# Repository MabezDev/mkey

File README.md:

## mKey

A mechanical keyboard based on an ESP32-S3, with firmware written in Rust.

[Click here to view the PCB & Schematic interactively in the browser](https://kicanvas.org/?github=https%3A%2F%2Fgithub.com%2FMabezDev%2Fmkey%2Ftree%2Fmain%2Fhardware%2Fboard)

## Flashing

The USB port is intended for flashing, as well as software USB usage. Version 1.0 of the board however has the DP and DM pins swapped, therefore to flash the board from the factory (or if the flash is wiped for any reason) you must flash via UART0. The pinout is as follows:

- TX is connected to the input side of D2 (COL1)
- RX is conncted to the input side of D3 (COL2)

## License

Licensed under either of:

- Apache License, Version 2.0 ([LICENSE-APACHE](LICENSE-APACHE) or http://www.apache.org/licenses/LICENSE-2.0)
- MIT license ([LICENSE-MIT](LICENSE-MIT) or http://opensource.org/licenses/MIT)
- CERN-OHL for the hardware files

at your option.

### Contribution

Unless you explicitly state otherwise, any contribution intentionally submitted for inclusion in
the work by you, as defined in the Apache-2.0 license, shall be dual licensed as above, without
any additional terms or conditions.

Contributions to the hardware will be licensed under the CERN-OHL license.

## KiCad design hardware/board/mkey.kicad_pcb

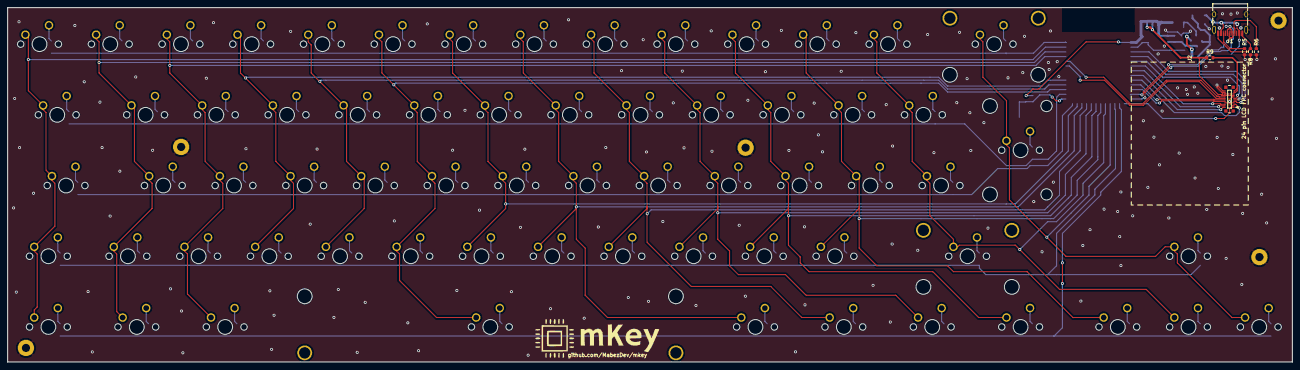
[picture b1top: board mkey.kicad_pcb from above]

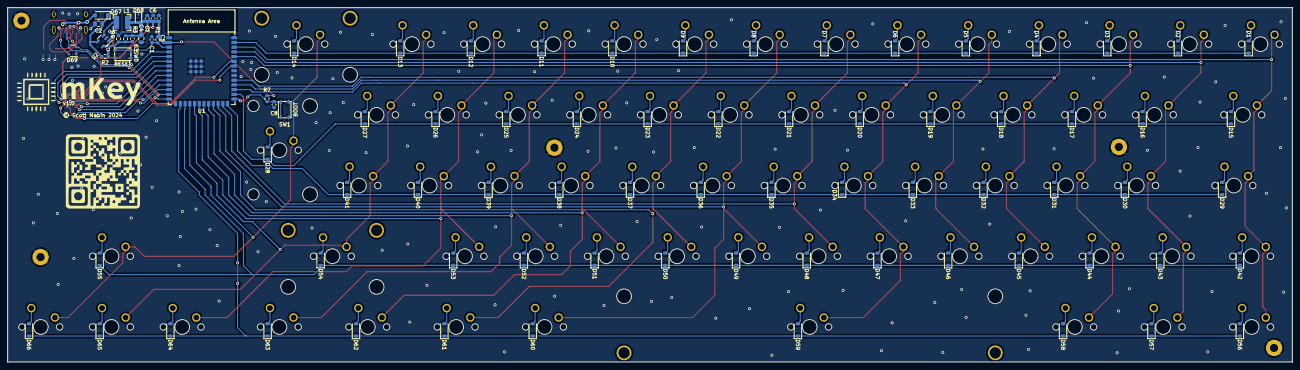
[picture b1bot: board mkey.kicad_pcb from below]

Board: 2 copper layers, 346.2 x 95.5 mm, 163 parts (87 on the bottom side), 112 nets.

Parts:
C1, C5: 1uF 16V; C_0603_1608Metric
C2, C4: 10uF 16V; C_0805_2012Metric
C3: 22pF 50V; C_0603_1608Metric
C6: 100nF 10V; C_0603_1608Metric
C7: 10nF 10V; C_0603_1608Metric
C8: 1nF 10V; C_0603_1608Metric
D1, D2, D3, D4, D5, D6, D7, D8, D9, D10, D11, D12, D13, D14, D15, D16, D17, D18, D19, D20, D21, D22, D23, D24, D25, D26, D27, D28, D29, D30, D31, D32, D33, D34, D35, D36, D37, D38, D39, D40, D41, D42, D43, D44, D45, D46, D47, D48, D49, D50, D51, D52, D53, D54, D55, D56, D57, D58, D59, D60, D61, D62, D63, D64, D65, D66: D_Small; D_SOD-123
D67: B5819W; D_SOD-123
D68: PESD3V3L1BA,115; D_SOD-323
D69: SP0503BAHT; SOT-143
J1: USB_C_REP_2.0; USB_C_Receptacle_HRO_TYPE-C-31-M-12
J2: 24 pin LCD FPC connector; CONN-SMD_24P-P0.40_X0400FVS-24-LPSN-LINEAR
L1: SPH4018H2R2MT (2.2uH 2.2A); L_Bourns-SRN4018
MX1, MX2, MX3, MX4, MX5, MX6, MX7, MX8, MX9, MX10, MX11, MX12, MX13, MX14, MX16, MX17, MX18, MX19, MX20, MX21, MX22, MX23, MX24, MX25, MX26, MX27, MX28, MX30, MX31, MX32, MX33, MX34, MX35, MX36, MX37, MX38, MX39, MX40, MX41, MX43, MX44, MX45, MX46, MX47, MX48, MX49, MX50, MX51, MX52, MX53, MX54, MX55, MX59, MX64, MX65, MX66: MX_SW_solder; SW_MX_1u
MX15: MX_SW_solder; SW_MX_1.5u
MX29: MX_SW_solder; SW_MX_1.75u
MX42, MX56, MX57, MX58, MX60, MX61, MX62, MX63: MX_SW_solder; SW_MX_1.25u
R1, R2, R7: 10kR 1%; R_0603_1608Metric
R3: 100kR 1%; R_0603_1608Metric
R4: 22k1R 1%; R_0603_1608Metric
R5, R6: 5k1R 1%; R_0603_1608Metric
R8: 0R 1%; R_0603_1608Metric
R9: 51.1R 1%; R_0603_1608Metric
S1: MX_stab; STAB_MX_P_6.25u
S2: MX_stab; STAB_MX_P_2u
S4: MX_stab; STAB_MX_P_2.75u
S5: MX_stab; STAB_MX_ISO-ROT
SW0, SW1: SW_Push; SW_SPST_PTS810
U1: ESP32-S3-WROOM-1
U2: SY8088; SOT-23-5

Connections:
+3V3: C3.1, C4.1, C5.1, C6.1, C7.1, D68.2 (A2), J2.9, J2.10, J2.15, J2.16, L1.2, R1.1, R3.1, R7.1, R9.2, U1.2 (3V3)
/Buck_Coil: L1.1, U2.3 (LX)
BOOT: C8.2, R7.2, SW1.1, U1.27 (GPIO0/BOOT)
CHIP_PU: C1.1, R1.2, SW0.1, U1.3 (EN)
COL0: MX1.1, MX15.1, MX29.1, MX42.1, MX56.1, U1.38 (GPIO2/TOUCH2/ADC1_CH1)
COL1: MX2.1, MX16.1, MX30.1, MX43.1, MX57.1, U1.37 (U0TXD/GPIO43/CLK_OUT1)
COL2: MX3.1, MX17.1, MX31.1, MX44.1, MX58.1, U1.36 (U0RXD/GPIO44/CLK_OUT2)
COL3: MX4.1, MX18.1, MX32.1, MX45.1, U1.31 (GPIO38/FSPIWP/SUBSPIWP)
COL4: MX5.1, MX19.1, MX33.1, MX46.1, U1.30 (SPIDQS/GPIO37/FSPIQ/SUBSPIQ)
COL5: MX6.1, MX20.1, MX34.1, MX47.1, MX59.1, U1.29 (SPIIO7/GPIO36/FSPICLK/SUBSPICLK)
COL6: MX7.1, MX21.1, MX35.1, MX48.1, U1.25 (GPIO48/SPICLK_N/SUBSPICLK_N_DIFF)
COL7: MX8.1, MX22.1, MX36.1, MX49.1, MX60.1, U1.24 (GPIO47/SPICLK_P/SUBSPICLK_P_DIFF)
COL8: MX9.1, MX23.1, MX37.1, MX50.1, MX61.1, U1.23 (GPIO21)
COL9: MX10.1, MX24.1, MX38.1, MX51.1, MX62.1, U1.22 (GPIO14/TOUCH14/ADC2_CH3/FSPIWP/FSPIDQS/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)
COL10: MX11.1, MX25.1, MX39.1, MX52.1, MX63.1, U1.21 (GPIO13/TOUCH13/ADC2_CH2/FSPIQ/FSPIIO7/S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)
COL11: MX12.1, MX26.1, MX40.1, MX53.1, MX64.1, U1.20 (GPIO12/TOUCH12/ADC2_CH1/FSPICLK/FSPIIO6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)
COL12: MX13.1, MX27.1, MX41.1, MX54.1, MX65.1, U1.19 (GPIO11/TOUCH11/ADC2_CH0/FSPID/FSPIIO5/S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)
COL13: MX14.1, MX28.1, MX55.1, MX66.1, U1.18 (GPIO10/TOUCH10/ADC1_CH9/FSPICS0/FSPIIO4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)
GND: C1.2, C2.2, C4.2, C5.2, C6.2, C7.2, C8.1, D68.1 (A1), D69.1 (A), J1.S1 (SHIELD), J2.2, J2.4, J2.8, J2.13, J2.14, J2.21, R4.2, R5.2, R6.2, R8.2, SW0.2, SW1.2, U1.1 (GND), U1.40 (GND), U1.41 (GND), U2.2 (GND)
LCD_CLK: J2.5, U1.4 (GPIO4/TOUCH4/ADC1_CH3)
LCD_D/C: J2.24, U1.9 (GPIO16/U0CTS/ADC2_CH5/XTAL_32K_N)
LCD_RESET: J2.1, U1.15 (GPIO3/TOUCH3/ADC1_CH2)
LCD_SIO0: J2.7, U1.6 (GPIO6/TOUCH6/ADC1_CH5)
LCD_SIO1: J2.6, U1.5 (GPIO5/TOUCH5/ADC1_CH4)
LCD_SIO2: J2.23, U1.8 (GPIO15/U0RTS/ADC2_CH4/XTAL_32K_P)
LCD_SIO3: J2.22, U1.7 (GPIO7/TOUCH7/ADC1_CH6)
unnamed: D1.2 (A), MX1.2
unnamed: D2.2 (A), MX2.2
unnamed: D3.2 (A), MX3.2
unnamed: D4.2 (A), MX4.2
unnamed: D5.2 (A), MX5.2
unnamed: D6.2 (A), MX6.2
unnamed: D7.2 (A), MX7.2
unnamed: D8.2 (A), MX8.2
unnamed: D9.2 (A), MX9.2
unnamed: D10.2 (A), MX10.2
unnamed: D11.2 (A), MX11.2
unnamed: D12.2 (A), MX12.2
unnamed: D13.2 (A), MX13.2
unnamed: D14.2 (A), MX14.2
unnamed: D15.2 (A), MX15.2
unnamed: D16.2 (A), MX16.2
unnamed: D17.2 (A), MX17.2
unnamed: D18.2 (A), MX18.2
unnamed: D19.2 (A), MX19.2
unnamed: D20.2 (A), MX20.2
unnamed: D21.2 (A), MX21.2
unnamed: D22.2 (A), MX22.2
unnamed: D23.2 (A), MX23.2
unnamed: D24.2 (A), MX24.2
unnamed: D25.2 (A), MX25.2
unnamed: D26.2 (A), MX26.2
unnamed: D27.2 (A), MX27.2
unnamed: D28.2 (A), MX28.2
unnamed: D29.2 (A), MX29.2
unnamed: D30.2 (A), MX30.2
unnamed: D31.2 (A), MX31.2
unnamed: D32.2 (A), MX32.2
unnamed: D33.2 (A), MX33.2
unnamed: D34.2 (A), MX34.2
unnamed: D35.2 (A), MX35.2
unnamed: D36.2 (A), MX36.2
unnamed: D37.2 (A), MX37.2
unnamed: D38.2 (A), MX38.2
unnamed: D39.2 (A), MX39.2
unnamed: D40.2 (A), MX40.2
unnamed: D41.2 (A), MX41.2
unnamed: D42.2 (A), MX42.2
unnamed: D43.2 (A), MX43.2
unnamed: D44.2 (A), MX44.2
unnamed: D45.2 (A), MX45.2
unnamed: D46.2 (A), MX46.2
unnamed: D47.2 (A), MX47.2
unnamed: D48.2 (A), MX48.2
unnamed: D49.2 (A), MX49.2
unnamed: D50.2 (A), MX50.2
unnamed: D51.2 (A), MX51.2
unnamed: D52.2 (A), MX52.2
unnamed: D53.2 (A), MX53.2
unnamed: D54.2 (A), MX54.2
unnamed: D55.2 (A), MX55.2
unnamed: D56.2 (A), MX56.2
unnamed: D57.2 (A), MX57.2
unnamed: D58.2 (A), MX58.2
unnamed: D59.2 (A), MX59.2
unnamed: D60.2 (A), MX60.2
unnamed: D61.2 (A), MX61.2
unnamed: D62.2 (A), MX62.2
unnamed: D63.2 (A), MX63.2
unnamed: D64.2 (A), MX64.2
unnamed: D65.2 (A), MX65.2
unnamed: D66.2 (A), MX66.2
unnamed: D67.2 (A), D69.4 (K), J1.A4 (VBUS), J1.A9 (VBUS), J1.B4 (VBUS), J1.B9 (VBUS)
unnamed: J1.A5 (CC1), R6.1
unnamed: J1.B5 (CC2), R5.1
unnamed: J1.A1 (GND), J1.A12 (GND), J1.B1 (GND), J1.B12 (GND), R8.1
unnamed: J2.11, J2.12, R9.1
unnamed: R2.2, U2.1 (EN)
unnamed: C3.2, R3.2, R4.1, U2.5 (FB)
ROW0: D1.1 (K), D2.1 (K), D3.1 (K), D4.1 (K), D5.1 (K), D6.1 (K), D7.1 (K), D8.1 (K), D9.1 (K), D10.1 (K), D11.1 (K), D12.1 (K), D13.1 (K), D14.1 (K), U1.39 (GPIO1/TOUCH1/ADC1_CH0)
ROW1: D15.1 (K), D16.1 (K), D17.1 (K), D18.1 (K), D19.1 (K), D20.1 (K), D21.1 (K), D22.1 (K), D23.1 (K), D24.1 (K), D25.1 (K), D26.1 (K), D27.1 (K), D28.1 (K), U1.28 (SPIIO6/GPIO35/FSPID/SUBSPID)
ROW2: D29.1 (K), D30.1 (K), D31.1 (K), D32.1 (K), D33.1 (K), D34.1 (K), D35.1 (K), D36.1 (K), D37.1 (K), D38.1 (K), D39.1 (K), D40.1 (K), D41.1 (K), U1.26 (GPIO45)
ROW3: D42.1 (K), D43.1 (K), D44.1 (K), D45.1 (K), D46.1 (K), D47.1 (K), D48.1 (K), D49.1 (K), D50.1 (K), D51.1 (K), D52.1 (K), D53.1 (K), D54.1 (K), D55.1 (K), U1.17 (GPIO9/TOUCH9/ADC1_CH8/FSPIHD/SUBSPIHD)
ROW4: D56.1 (K), D57.1 (K), D58.1 (K), D59.1 (K), D60.1 (K), D61.1 (K), D62.1 (K), D63.1 (K), D64.1 (K), D65.1 (K), D66.1 (K), U1.16 (GPIO46)
TEAR EFFECT: J2.3, U1.10 (GPIO17/U1TXD/ADC2_CH6)
TP_INT: J2.17, U1.35 (MTMS/GPIO42)
TP_RST: J2.18, U1.34 (MTDI/GPIO41/CLK_OUT1)
TP_SCL: J2.20, U1.12 (GPIO8/TOUCH8/ADC1_CH7/SUBSPICS1)
TP_SDA: J2.19, U1.11 (GPIO18/U1RXD/ADC2_CH7/CLK_OUT3)
USB_D+: D69.3 (K), J1.A6 (D+), J1.B6 (D+), U1.14 (GPIO20/U1CTS/ADC2_CH9/CLK_OUT1/USB_D+)
USB_D-: D69.2 (K), J1.A7 (D-), J1.B7 (D-), U1.13 (GPIO19/U1RTS/ADC2_CH8/CLK_OUT2/USB_D-)
VBUS: C2.1, D67.1 (K), R2.1, U2.4 (IN)

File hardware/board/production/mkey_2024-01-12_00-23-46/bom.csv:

Designator,Footprint,Quantity,Value,LCSC Part #
"_4, _3, _2, ",,4,,
"C1, C5",0603,2,1uF 16V,C52923
"C2, C4",0805,2,10uF 16V,C15850
C3,0603,1,22pF 50V,C1653
C6,0603,1,100nF 10V,C1525
C7,0603,1,10nF 10V,C15195
"D1, D10, D11, D12, D13, D14, D15, D16, D17, D18, D19, D2, D20, D21, D22, D23, D24, D25, D26, D27, D28, D29, D3, D30, D31, D32, D33, D34, D35, D36, D37, D38, D39, D4, D40, D41, D42, D43, D44, D45, D46, D47, D48, D49, D5, D50, D51, D52, D53, D54, D55, D56, D57, D58, D59, D6, D60, D61, D62, D63, D64, D65, D66, D7, D8, D9",D_SOD-123,66,D_Small,
D67,D_SOD-123,1,B5819W,C8598
D68,D_SOD-323,1,"PESD3V3L1BA,115",
D69,SOT-143,1,SP0503BAHT,
J1,USB_C_Receptacle_HRO_TYPE-C-31-M-12,1,USB_C_REP_2.0,
J2,CONN-SMD_24P-P0.40_X0400FVS-24-LPSN-LINEAR,1,24 pin LCD FPC connector,
L1,L_Bourns-SRN4018,1,SPH4018H2R2MT (2.2uH 2.2A),C370436
"MX1, MX10, MX11, MX12, MX13, MX14, MX16, MX17, MX18, MX19, MX2, MX20, MX21, MX22, MX23, MX24, MX25, MX26, MX27, MX28, MX3, MX30, MX31, MX32, MX33, MX34, MX35, MX36, MX37, MX38, MX39, MX4, MX40, MX41, MX43, MX44, MX45, MX46, MX47, MX48, MX49, MX5, MX50, MX51, MX52, MX53, MX54, MX55, MX59, MX6, MX64, MX65, MX66, MX7, MX8, MX9",SW_MX_1u,56,MX_SW_solder,
MX15,SW_MX_1.5u,1,MX_SW_solder,
MX29,SW_MX_1.75u,1,MX_SW_solder,
"MX42, MX56, MX57, MX58, MX60, MX61, MX62, MX63",SW_MX_1.25u,8,MX_SW_solder,
"R1, R2, R7",0603,3,10kR 1%,C25744
R3,0603,1,100kR 1%,C25741
R4,0603,1,22k1R 1%,C43473
"R5, R6",0603,2,5k1R 1%,C25905
R8,0603,1,0R 1%,C17168
R9,0603,1,51.1R 1%,C25744
S1,STAB_MX_P_6.25u,1,MX_stab,
S2,STAB_MX_P_2u,1,MX_stab,
S4,STAB_MX_P_2.75u,1,MX_stab,
S5,STAB_MX_ISO-ROT,1,MX_stab,
"SW0, SW1",SW_SPST_PTS810,2,SW_Push,C116501
U1,ESP32-S3-WROOM-1,1,ESP32-S3-WROOM-1,
U2,SOT-23-5,1,SY8088,C479072

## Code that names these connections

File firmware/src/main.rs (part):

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    io.set_interrupt_handler(display::te);
    interrupt::enable(Interrupt::GPIO, Priority::Priority2);

    let sclk = peripherals.GPIO4;
    let sio0 = peripherals.GPIO6;
    let sio1 = peripherals.GPIO5;
    let sio2 = peripherals.GPIO15;
    let sio3 = peripherals.GPIO7;
    let cs = peripherals.GPIO16;
    let mut reset = Output::new(peripherals.GPIO3, Level::Low, Default::default());

    let mut te_pin = Input::new(
        peripherals.GPIO17,
        InputConfig::default().with_pull(Pull::Down),
    );
    te_pin.listen(esp_hal::gpio::Event::RisingEdge);
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        [Input<'static>; 14],
        [
            Input::new(
                peripherals.GPIO2,
                InputConfig::default().with_pull(Pull::Up)
            ), // 0
            Input::new(
                peripherals.GPIO43,
                InputConfig::default().with_pull(Pull::Up)
            ), // 1
            Input::new(
                peripherals.GPIO44,
                InputConfig::default().with_pull(Pull::Up)
            ), // 2
            Input::new(
                peripherals.GPIO38,
                InputConfig::default().with_pull(Pull::Up)
            ), // 3
            Input::new(
                peripherals.GPIO37,
                InputConfig::default().with_pull(Pull::Up)
            ), // 4
            Input::new(
                peripherals.GPIO36,
                InputConfig::default().with_pull(Pull::Up)
            ), // 5
            Input::new(
                peripherals.GPIO48,
                InputConfig::default().with_pull(Pull::Up)
            ), // 6
            Input::new(
                peripherals.GPIO47,
                InputConfig::default().with_pull(Pull::Up)
            ), // 7
            Input::new(
                peripherals.GPIO21,
                InputConfig::default().with_pull(Pull::Up)
            ), // 8
            Input::new(
                peripherals.GPIO14,
                InputConfig::default().with_pull(Pull::Up)
            ), // 9
            Input::new(
                peripherals.GPIO13,
                InputConfig::default().with_pull(Pull::Up)
            ), // 10
            Input::new(
                peripherals.GPIO12,
                InputConfig::default().with_pull(Pull::Up)
            ), // 11
            Input::new(
                peripherals.GPIO11,
                InputConfig::default().with_pull(Pull::Up)
            ), // 12
            Input::new(
                peripherals.GPIO10,
                InputConfig::default().with_pull(Pull::Up)
            ), // 13
        ]
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    let rows = make_static!(
        [Output<'static>; 5],
        [
            Output::new(peripherals.GPIO1, Level::Low, Default::default()), // 0
            Output::new(peripherals.GPIO35, Level::Low, Default::default()), // 1
            Output::new(peripherals.GPIO45, Level::Low, Default::default()), // 2
            Output::new(peripherals.GPIO9, Level::Low, Default::default()), // 3
            Output::new(peripherals.GPIO46, Level::Low, Default::default()), // 4
        ]
    );

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                });
            } else {
                let device =
                    Usb::new_fs(peripherals.USB_FS, peripherals.GPIO20, peripherals.GPIO19);
                executor.run(|spawner| {
                    spawner.spawn(keyboard::matrix(columns, rows, signal).unwrap());
                    spawner.spawn(keyboard::usb(device, signal).unwrap());
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
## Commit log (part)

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2023-09-24 Initial schematic bringup
    * Add esp32s3
    * Add switches based on https://gist.github.com/MabezDev/e74a6ef222bb8367cc60e5eef9f082c7
    * Add power/usb and boot circuitry based on the esp-rust-board
2023-09-28 small updates
2024-01-01 Flipped usb c and condensed the vcc filtering
2024-01-02 place and route buttons
2024-01-03 Add display connector to schematic, thicken power traces
2024-01-10 Fix all DRC errors, just warnings to look at
2024-01-11 readme and licenses
2024-01-12 Fix fpc connector schematic
2024-01-18 Initial fw with dp dm swap work around
2024-01-18 qio working? can read back some values, one seems correct, the other does not match the reset value...
2024-01-19 refactor operations, still not really working
2024-01-21 move lib back to board, kicad doesn't seem to follow paths outside of the proj. Add 3d model to usb port
2024-03-03 display working on devboard with correct colours
2024-03-10 Add sin colour animation from https://github.com/bjoernQ/rust-esp32s3-ili9341
2024-03-12 fps counter
2024-04-30 basic usb support, writes 'a' on any new key press
2026-03-29 add UK ISO keymap with debounced matrix scanning and proper HID reports
    Replace the placeholder 'always send A' logic with a full keymap-driven
    approach: a 5×14 KEYMAP table maps each (row, col) to HID keycodes and
    modifier bits, the matrix task debounces key state and builds complete
    KeyboardReports (6KRO + modifiers), and the USB task forwards them directly.
2026-03-30 fix spacebar mapping and simplify Fn combo detection
    Space was only mapped to col 4 (unverified schematic guess); restore
    it across cols 3-7 to cover the actual switch position. Col 8 remains
    the Fn key as confirmed by user.
    Simplify combo detection to use direct (row, col) position checks
    instead of keymap keycode lookups, eliminating a potential mismatch.
2026-03-30 add USB init diagnostic logging before PHY takeover
2026-03-30 flush JTAG serial after printing previous panic message
2026-03-30 fix boot hang: use non-blocking JTAG writes, remove 10s delay
    Three issues causing boot hang:
    - UsbSerialJtagTx::write() blocks waiting for host to read FIFO;
    switch to write_byte_nb/flush_tx_nb which drop data if FIFO full
    - check_previous_panic() was doing blocking JTAG serial writes;
    remove them, let CDC task handle output after USB enumerates
    - 10-second delay on panic detection removed; display starts immediately
2026-03-30 rename log module to logger to avoid shadowing the log crate
    mod log shadowed the log crate, causing ::log:: resolution issues
    that crashed on boot when log::init() was called. Renaming to
    logger eliminates the ambiguity.
2026-03-31 intial scad design
2026-04-09 chamfer back-right corner to balance off-center display
2026-04-13 thicken display shelf with curved asymmetric frame
    The uniform 0.8 mm shelf picture frame was the weakest part of the
    overlay after the stepped display cut landed. X is constrained to
    1.20 mm by the module bezel, but Y has 2.26 mm of bezel to work with,
    so the shelf is split into independent shelf_frame_x / shelf_frame_y:
    - shelf_frame_x bumped 0.8 → 1.0 mm (+25% on the long edges,
    where the weakest beams live)
2026-04-14 add overlay locating tongue + magnet pocket features
    Adds two optional features (both behind toggles at the top of case.scad) to
    lock the overlay to the tray instead of relying on gasket friction alone:
    - ENABLE_OVERLAY_RABBET: an inverted "tongue" on the tray wall top inside
    edge that drops into a matching recess in the overlay underside. The
    tongue/recess ring is notched at each of the 9 gasket slot Y locations
    so the plate-tab drop-in path stays clear.
2026-04-14 tune case tolerances for JLC3DP SLA pre-fab review
    Raise disp_cut_tol 0.15 → 0.20 to clear JLC3DP's 0.2 mm assembly-
    clearance rule under SLA's ±0.2 mm <100 mm tolerance; worst-case pocket
    shrink goes from 0.05 mm interference to 0.0 mm clearance. Grow the
    overlay locating tongue from 1.3 × 1.0 mm to 1.5 × 1.5 mm to meet
    JLC3DP's 1.5 mm recommended minimum for positioning/snap features on
    SLA. Pin the intended 3D-print process in the file header so future
2026-04-14 add JLC3DP production artefacts for mkey case
    Moves the OpenSCAD source and its parameter set into 3d/case/ alongside
    the exact STLs that were submitted to JLC3DP: mkey_tray.stl (363.238 x
    110.825 x 33.429 mm, 7056 tris) and mkey_overlay.stl (367.238 x 114.825
    x 15.045 mm, 2284 tris). Both are manifold, both reproduce bit-for-bit
    from case.scad + case.json with all asserts passing.
    Submitted order:
2026-04-16 fix 3 pre-fab review issues in case.scad for JLC3DP SLA
    Full design review against JLC3DP SLA design rules found three issues:
    1. Owner initials chirality (deco_owner_initials): mirror([1,0,0]) →
    mirror([0,1,0]). Flipping the case toward the viewer rotates around X,
    which negates Y but preserves X — the old X-mirror produced backwards
    text; Y-mirror correctly pre-compensates the vertical glyph inversion.
    2. Year text stroke width (deco_year_size): 3.8 → 5.0 mm. At 3.8 mm cap
2026-04-16 disable top logo above the display
2026-04-17 widen cosmetic strokes and tongue to clear JLC3DP slop margins
    Part of the 2026-04-17 pre-fab review (B–F marginals). Previous values
    sat exactly on JLC3DP floors; these bumps give ≥0.2 mm headroom so the
    full ±0.2 mm SLA fab slop fits inside the margin without narrowing any
    printed feature below spec.
    - deco_stripe_width 0.9 → 1.0 mm (pinstripe groove)
    - deco_year_size 5.5 → 6.0 mm (underside year row, stroke 0.90 mm)
2026-04-17 fix thin wall warnings around magnet pockets for JLC3DP
    Split wall_t into tray_wall_t (5.3mm) and overlay_wall_t (4.8mm) so the
    tray extends 0.5mm outward on all sides while overlay stays unchanged.
    This increases the magnet pocket outer cheek without affecting the
    mating interface.
    Also reduced magnet_d from 2.5mm to 2.3mm (still fits 2mm magnets with
    0.3mm clearance) to improve the inner cheek.
2026-04-17 add soft rounded corners to tray and overlay edges
    - Add tray_corner_r parameter (0.75mm) and use rounded_wedge_box for tray
    - Reduce overlay_corner_r from 3.0mm to 0.75mm for subtle edge softening
    - Fix overlay corner: use non-rounded wedge_box for inner cavity subtraction
    to preserve outer corner radius (was being cut away by larger inner radius)
    - Remove bottom edge chamfers (not needed with corner rounding)
2026-04-17 extend display cutout height to clear chamfered top surface
    The 0.02mm margin wasn't enough to cut through the 1.2mm chamfer
    geometry, leaving artifacts over the display housing.
2026-04-20 drop display retainer and shrink pad recess for 3 mm floor
    Two pre-existing assertions blocked STL generation under the new
    case dimensions on this branch:
    - retainer_t (1.2) > disp_pocket_d - disp_glass_t (0.44) once top_t
    shrunk to 3.5. The module is already glue-bonded to the shelf
    underside (primary mounting method), so drop the retainer feature
    entirely — remove the param, module, assembly block, and SHOW flag.
2026-04-20 shift USB cutout to track installed plate Z under gasket scheme
    The plate rests on the bottom foam gasket inside each slot, so its
    installed Z is `slot_bot + bot_gasket_installed` — not the design-nominal
    plate midplane that the slot is sized around. With a 1.5 mm bottom
    gasket fitting a slot_bot_below_plate budget of ~2.82 mm, the plate
    settles ~1.32 mm below nominal; the USB receptacle is bonded to the PCB
    which rides the switches bonded to the plate, so it drops with them.
2026-04-20 add corner breaks so each rib neck snaps against a single wall
    The wall and floor breakaway necks overlapped at the front-floor and
    back-floor corners, fusing the rib to two surfaces simultaneously and
    preventing a clean snap in either axis. Remove the rib entirely in
    the rib_neck_len × rib_neck_len corner cubes so each neck is an
    independent single-wall attachment.
2026-04-21 bump text sizes and enable owner initials by default
    Increase logo wordmark and owner initials cap height from 7.5/8.0
    to 9.0 mm so narrow counter openings (e, 0, 2) clear the JLC3DP
    0.8 mm engraved-detail floor. Enable DECO_OWNER_INITIALS by default.
2026-04-21 redesign screw retention for JLC3DP SLA compliance
    Wall-top captive bolt approach: bolt inserted tip-first from the wall
    top, head catches on a counterbore step 3.2 mm below the surface, shaft
    protrudes 1.5 mm above into the overlay nut. Total hole depth 3.2 mm
    (within JLC's 6 mm max for 2 mm dia holes).
    Shifted screw center from wall_t/2 (2.4 mm) to 3.0 mm from the outer
    face, improving overlay nut outer cheek from 0.7 → 1.3 mm AF.
2026-04-21 fix stale inline arithmetic comments in case.scad
    Seven trailing "// value" annotations were stale from prior pre-fab reviews
    that raised disp_cut_tol (0.15 → 0.30) and slot_tol (0.4 → 0.6) without
    updating the human-readable comments. The executable code is unchanged —
    only the documentation is corrected to match the actual computed values.
2026-04-21 pre-fab: address warnings — grow screw pocket + nut AF, doc clarifications
    Continues the pre-fab review. All seven warnings from the review are
    addressed either by geometry change (W1, W2) or README updates
    (W3–W6 + two doc-drift fixes).
    W1: screw_pocket_d 3.0 → 3.4 mm. At 3.0 mm the JLC3DP ±0.3 mm hole
    tolerance shrank worst-case to 2.7 mm and the 2.6 mm M1.4 SHCS head
    had only 0.05 mm/side clearance — below the 0.2 mm static-assembly
2026-04-22 pre-fab: add 0.1 mm boolean overlap to support rib junctions
    Without overlap the rib slab's faces are coplanar with the tray walls
    and floor, which produces degenerate CGAL topology on some OpenSCAD
    versions (manifold union of exactly-coincident faces). Adding 0.1 mm
    of overlap into the walls and floor ensures a clean boolean union.
2026-04-22 pre-fab: blunt chamfer fill apex to eliminate back-wall knife-edge
    The back-wall chamfer fill was a triangle tapering to zero Y-depth
    at z = cb, creating sub-2 mm wall sections that violate JLC3DP SLA
    minimums. Replace with a trapezoid: chamfer_fill_min_y (2.0 mm)
    keeps the apex blunted. Wall grows from tray_wall_t at z = bottom_t
    to tray_wall_t + 2.0 mm at z = cb — extra thickness eats unused
    cavity space below the plate/PCB stack.
2026-04-23 pre-fab: add anti-warp snap-off tie bars to overlay key opening
    The overlay's large key void (~288 × 96 mm) leaves the surrounding
    frame prone to bowing from SLA cure shrinkage. Add 5 flat rectangular
    tie bars spanning front-to-back (Y direction) across the main key
    field void at ~48 mm pitch.
    Each bar is 4 mm wide × 1.5 mm tall, sitting flush against the slab
    underside. A 1.0 mm neck (matching tray rib_neck for JLC3DP spec)
2026-04-23 pre-fab: flip overlay tie bars flush with top (build-plate face)
    Overlay prints top-down, so supports need to bond at the top surface
    not the underside. Repositions bars from top_z - top_t to top_z - bar_h.
2026-04-24 refactor: remove CAD-modelled print supports in favour of slicer-generated supports
    Print supports (tray anti-warp ribs, overlay tie bars) are better handled
    by the slicer (Lychee/ChiTuBox) which can optimise placement per-printer.
    Removes PRINT_SUPPORTS toggle, all support geometry modules/variables/
    assertions, the --supports build flag, and updates manufacture notes,
    README, test matrix, and JSON presets accordingly.

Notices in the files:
hardware/board/mkey.kicad_pcb:
© Scott Mabin 2024
